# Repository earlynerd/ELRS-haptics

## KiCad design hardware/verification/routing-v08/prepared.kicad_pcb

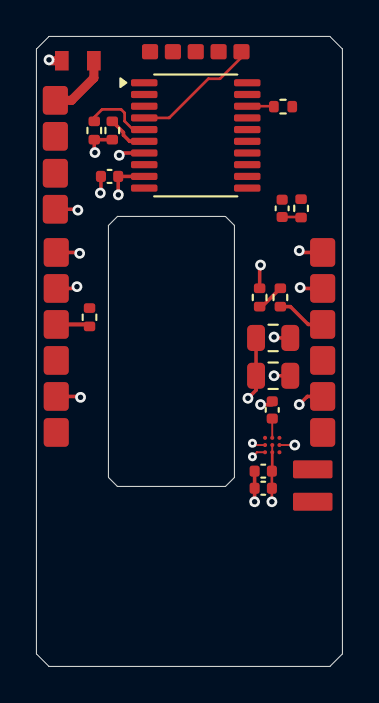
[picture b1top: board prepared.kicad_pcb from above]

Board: 4 copper layers, 17.0 x 35.0 mm, 23 parts (0 on the bottom side), 16 nets.

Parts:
C23, C24, C160: 100n; C_0402_1005Metric
C25: 1u; C_0402_1005Metric
C161: 10u; C_0805_2012Metric
C162: 10n; C_0402_1005Metric
C163: 22u 10V X5R; C_0805_2012Metric
F106: 250mA FAST; Fuse_Littelfuse_467_0603
J124: CHAIN IN; WirePads_6_P2mm
J125: CHAIN OUT; WirePads_6_P2mm
J126: ICE / INITIAL FLASH; WirePads_5_P1.27mm
J127: NTC (optional); WirePads_2_P2mm
J206: PROTECTED CELL 90mAh; WirePads_2_P2mm
M7: VLV041235L; Vybronics_VLV041235L_FPC_Contact_Draft
R20, R21: 4.7k; R_0402_1005Metric
R160: 0; R_0402_1005Metric
R161: 33; R_0402_1005Metric
R162, R163: 100k; R_0402_1005Metric
R165: 10k 1%; R_0402_1005Metric
U9: DRV2625; DRV2625_YFF_9_0.4mm
U24: M2003FC1AE; TSSOP-20_4.4x6.5mm_P0.65mm

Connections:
/Eight ring pods/Pod 6 / U24/CELL_POS: F106.1, J206.1
/Eight ring pods/Pod 6 / U24/CELL_TEMP: C162.1, J127.1, R165.2, U24.2
/Eight ring pods/Pod 6 / U24/DRV_REG: C24.1, U9.A2
/Eight ring pods/Pod 6 / U24/LOCAL_SCL: R21.2, U9.C1, U24.6
/Eight ring pods/Pod 6 / U24/LOCAL_SDA: R20.2, U9.B1, U24.5
/Eight ring pods/Pod 6 / U24/LRA_N: M7.2, U9.C3
/Eight ring pods/Pod 6 / U24/LRA_P: M7.1, U9.A3
/Eight ring pods/Pod 6 / U24/UART_RX_LOCAL: J126.4, R160.2, R162.2, U24.18
/Eight ring pods/Pod 6 / U24/UART_TX_LOCAL: J126.3, R161.1, R163.2, U24.8
GND: C23.2, C24.2, C25.2, C160.2, C161.2, C162.2, C163.2, J124.2, J125.2, J126.2, J127.2, J206.2, U9.B3, U24.7
POD_3V3: C23.1, C25.1, C160.1, C161.1, C163.1, J124.1, J125.1, J126.1, R20.1, R21.1, R162.1, R163.1, R165.1, U9.B2, U9.C2, U24.9
RING_D6: J124.3, R160.1
RING_D7: J125.3, R161.2
RING_RETURN: J124.6, J125.6
RING_nRESET: J124.4, J125.4, J126.5, U24.4
VBAT: F106.2, J124.5, J125.5

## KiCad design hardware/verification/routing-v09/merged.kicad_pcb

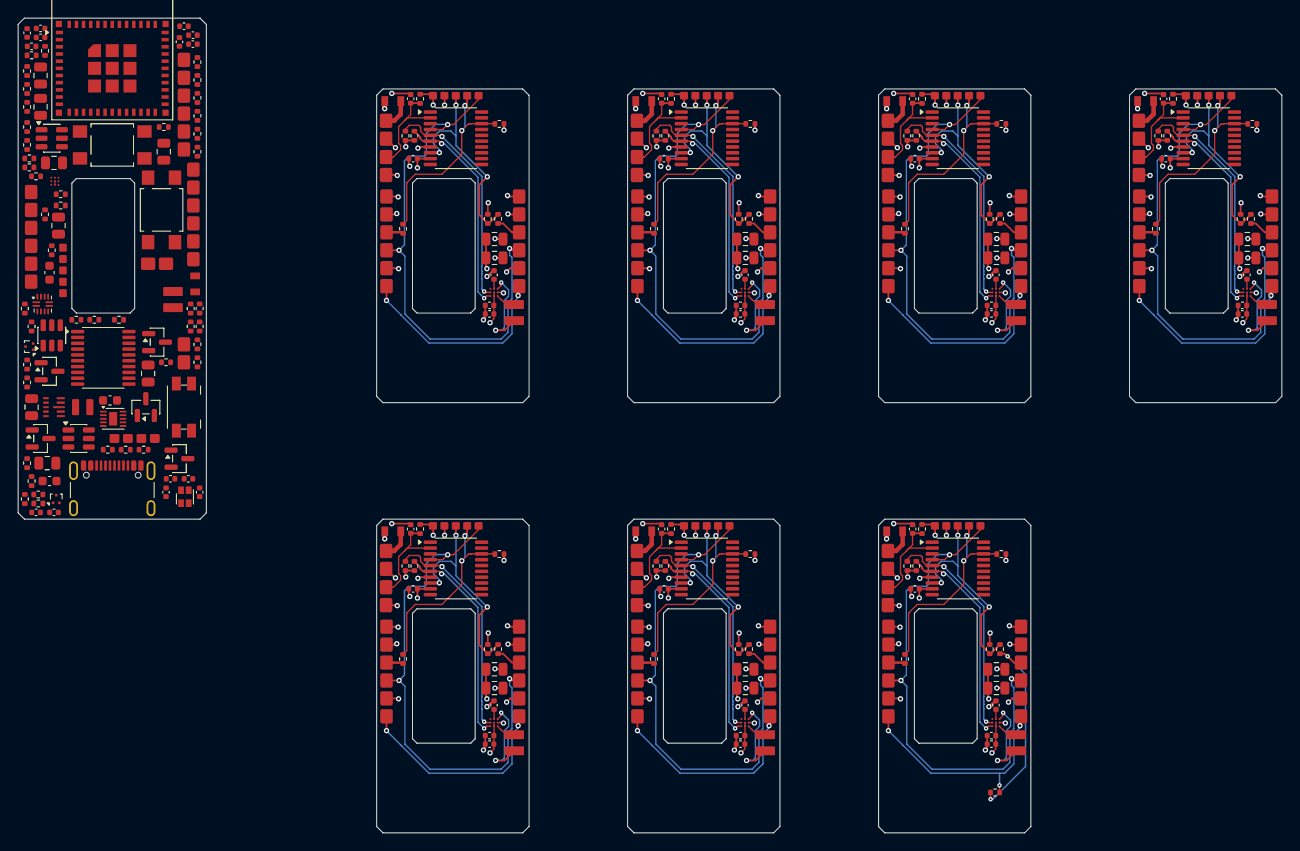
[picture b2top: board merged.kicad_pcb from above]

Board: 4 copper layers, 141.0 x 90.9 mm, 261 parts (0 on the bottom side), 133 nets.

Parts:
C1, C7, C10, C13, C16, C19, C22, C25, C28, C41, C43: 1u; C_0402_1005Metric
C2, C5, C6, C8, C9, C11, C12, C14, C15, C17, C18, C20, C21, C23, C24, C26, C27, C31, C100, C110, C120, C130, C140, C150, C160, C170: 100n; C_0402_1005Metric
C3, C101, C111, C121, C131, C141, C151, C161, C171: 10u; C_0805_2012Metric
C29, C30: TUNE / DNP; C_0402_1005Metric
C32, C34, C36: 1u 10V; C_0603_1608Metric
C33: 100n 10V; C_0402_1005Metric
C35, C37, C40: 10u 10V; C_0805_2012Metric
C38, C39: 22u 10V; C_0805_2012Metric
C42: 4.7n 25V; C_0402_1005Metric
C102, C112, C122, C132, C142, C152, C162, C172: 10n; C_0402_1005Metric
C103, C113, C123, C133, C143, C153, C163, C173: 22u 10V X5R; C_0805_2012Metric
D1: LTST-C19HE1WT; LED_LiteOn_LTST-C19HE1WT
F100, F101, F102, F103, F104, F105, F106, F107: 250mA FAST; Fuse_Littelfuse_467_0603
J1: ESP UART / BOOT / RESET; WirePads_6_P2mm
J2: USB4105-GF-A; USB_C_Receptacle_GCT_USB4105-xx-A_16P_TopMnt_Horizontal
J3: VBAT BUS + NTC; WirePads_4_P1.5mm
J100, J104, J108, J112, J116, J120, J124, J128: CHAIN IN; WirePads_6_P2mm
J101, J105, J109, J113, J117, J121, J125, J129: CHAIN OUT; WirePads_6_P2mm
J102, J106, J110, J114, J118, J122, J126, J130: ICE / INITIAL FLASH; WirePads_5_P1.27mm
J103, J107, J111, J115, J119, J123, J127, J131: NTC (optional); WirePads_2_P2mm
J200, J201, J202, J203, J204, J205, J206, J207: PROTECTED CELL 90mAh; WirePads_2_P2mm
L1: 0.47uH; L_Murata_DFE201612E
M1, M2, M3, M4, M5, M6, M7, M8: VLV041235L; Vybronics_VLV041235L_FPC_Contact_Draft
Q1, Q2, Q3, Q4, Q5: 2N7002; SOT-23
R1, R2, R8, R9, R10, R11, R12, R13, R14, R15, R16, R17, R18, R19, R20, R21, R22, R23: 4.7k; R_0402_1005Metric
R3, R4, R5, R6, R27, R36, R37: 10k; R_0402_1005Metric
R7, R30, R31, R32, R33, R34, R38, R39, R43, R45, R48, R50, R52, R102, R103, R112, R113, R122, R123, R132, R133, R142, R143, R152, R153, R162, R163, R172, R173: 100k; R_0402_1005Metric
R24, R25: 22; R_0402_1005Metric
R26: 887k 1%; R_0402_1005Metric
R28: 62k 1%; R_0402_1005Metric
R29: 43k 1%; R_0402_1005Metric
R35: 1M; R_0402_1005Metric
R40: 511k 1%; R_0402_1005Metric
R41: 91k 1%; R_0402_1005Metric
R42, R101, R111, R121, R131, R141, R151, R161, R171: 33; R_0402_1005Metric
R44, R46: 100; R_0402_1005Metric
R47, R49, R51: 2.2k; R_0402_1005Metric
R53, R100, R110, R120, R130, R140, R150, R160, R170: 0; R_0402_1005Metric
R105, R115, R125, R135, R145, R155, R165, R175: 10k 1%; R_0402_1005Metric
SW1: ESP RESET; SW_SPST_TL3305A
SW2: ESP BOOT; SW_SPST_TL3305A
SW3: WAKE / SHIP; Panasonic_EVQPUJ_EVQPUA
U1: ESP32-C6-MINI-1
U3, U4, U5, U6, U7, U8, U9, U10: DRV2625; DRV2625_YFF_9_0.4mm
U11: BQ25186DLH; Texas_DLH0010A_WSON-10-1EP_2.2x2mm_P0.4mm_EP0.9x1.5mm
U12: TPS63802DLA; TPS63802_DLA0010A
U13: TUSB320LAIRWB; Texas_X2QFN-12_1.6x1.6mm_P0.4mm
U14, U15: TPD2EUSB30; Texas_DRT-3
U16: TPS2553DBV; SOT-23-6
U17: TS5A3159DBV; SOT-23-6
U18, U19, U20, U21, U22, U23, U24, U25: M2003FC1AE; TSSOP-20_4.4x6.5mm_P0.65mm
U26: TPS22918DBV; SOT-23-6

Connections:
3V3: C2.1, C3.1, C31.1, C38.1, C39.1, C41.1, D1.4, J1.1, R1.1, R2.1, R3.1, R4.1, R5.1, R27.1, R36.1, R37.1, R40.1, R48.1, R50.1, R52.1, U1.3, U12.6, U13.12, U26.1
/Charger and regulated supply/CHG_nCE: Q1.3, R38.2, U11.4
/Charger and regulated supply/PACK_TS: J3.3, SW3.1, U11.6
/Charger and regulated supply/REG_FB: R40.2, R41.1, U12.4
/Charger and regulated supply/SW_L1: L1.1, U12.9
/Charger and regulated supply/SW_L2: L1.2, U12.7
/Charger and regulated supply/SYS: C35.1, C37.1, R38.1, U11.1, U12.1, U12.10
/ESP reset, boot and decoupling/LED_B_K: D1.3, R51.2
/ESP reset, boot and decoupling/LED_G_K: D1.2, R49.2
/ESP reset, boot and decoupling/LED_R_K: D1.1, R47.2
/Eight ring pods/Pod 0 / U18/CELL_POS: F100.1, J200.1
/Eight ring pods/Pod 0 / U18/CELL_TEMP: C102.1, J103.1, R105.2, U18.2
/Eight ring pods/Pod 0 / U18/DRV_REG: C6.1, U3.A2
/Eight ring pods/Pod 0 / U18/LOCAL_SCL: R9.2, U3.C1, U18.6
/Eight ring pods/Pod 0 / U18/LOCAL_SDA: R8.2, U3.B1, U18.5
/Eight ring pods/Pod 0 / U18/LRA_N: M1.2, U3.C3
/Eight ring pods/Pod 0 / U18/LRA_P: M1.1, U3.A3
/Eight ring pods/Pod 0 / U18/UART_RX_LOCAL: J102.4, R100.2, R102.2, U18.18
/Eight ring pods/Pod 0 / U18/UART_TX_LOCAL: J102.3, R101.1, R103.2, U18.8
/Eight ring pods/Pod 1 / U19/CELL_POS: F101.1, J201.1
/Eight ring pods/Pod 1 / U19/CELL_TEMP: C112.1, J107.1, R115.2, U19.2
/Eight ring pods/Pod 1 / U19/DRV_REG: C9.1, U4.A2
/Eight ring pods/Pod 1 / U19/LOCAL_SCL: R11.2, U4.C1, U19.6
/Eight ring pods/Pod 1 / U19/LOCAL_SDA: R10.2, U4.B1, U19.5
/Eight ring pods/Pod 1 / U19/LRA_N: M2.2, U4.C3
/Eight ring pods/Pod 1 / U19/LRA_P: M2.1, U4.A3
/Eight ring pods/Pod 1 / U19/UART_RX_LOCAL: J106.4, R110.2, R112.2, U19.18
/Eight ring pods/Pod 1 / U19/UART_TX_LOCAL: J106.3, R111.1, R113.2, U19.8
/Eight ring pods/Pod 2 / U20/CELL_POS: F102.1, J202.1
/Eight ring pods/Pod 2 / U20/CELL_TEMP: C122.1, J111.1, R125.2, U20.2
/Eight ring pods/Pod 2 / U20/DRV_REG: C12.1, U5.A2
/Eight ring pods/Pod 2 / U20/LOCAL_SCL: R13.2, U5.C1, U20.6
/Eight ring pods/Pod 2 / U20/LOCAL_SDA: R12.2, U5.B1, U20.5
/Eight ring pods/Pod 2 / U20/LRA_N: M3.2, U5.C3
/Eight ring pods/Pod 2 / U20/LRA_P: M3.1, U5.A3
/Eight ring pods/Pod 2 / U20/UART_RX_LOCAL: J110.4, R120.2, R122.2, U20.18
/Eight ring pods/Pod 2 / U20/UART_TX_LOCAL: J110.3, R121.1, R123.2, U20.8
/Eight ring pods/Pod 3 / U21/CELL_POS: F103.1, J203.1
/Eight ring pods/Pod 3 / U21/CELL_TEMP: C132.1, J115.1, R135.2, U21.2
/Eight ring pods/Pod 3 / U21/DRV_REG: C15.1, U6.A2
/Eight ring pods/Pod 3 / U21/LOCAL_SCL: R15.2, U6.C1, U21.6
/Eight ring pods/Pod 3 / U21/LOCAL_SDA: R14.2, U6.B1, U21.5
/Eight ring pods/Pod 3 / U21/LRA_N: M4.2, U6.C3
/Eight ring pods/Pod 3 / U21/LRA_P: M4.1, U6.A3
/Eight ring pods/Pod 3 / U21/UART_RX_LOCAL: J114.4, R130.2, R132.2, U21.18
/Eight ring pods/Pod 3 / U21/UART_TX_LOCAL: J114.3, R131.1, R133.2, U21.8
/Eight ring pods/Pod 4 / U22/CELL_POS: F104.1, J204.1
/Eight ring pods/Pod 4 / U22/CELL_TEMP: C142.1, J119.1, R145.2, U22.2
/Eight ring pods/Pod 4 / U22/DRV_REG: C18.1, U7.A2
/Eight ring pods/Pod 4 / U22/LOCAL_SCL: R17.2, U7.C1, U22.6
/Eight ring pods/Pod 4 / U22/LOCAL_SDA: R16.2, U7.B1, U22.5
/Eight ring pods/Pod 4 / U22/LRA_N: M5.2, U7.C3
/Eight ring pods/Pod 4 / U22/LRA_P: M5.1, U7.A3
/Eight ring pods/Pod 4 / U22/UART_RX_LOCAL: J118.4, R140.2, R142.2, U22.18
/Eight ring pods/Pod 4 / U22/UART_TX_LOCAL: J118.3, R141.1, R143.2, U22.8
/Eight ring pods/Pod 5 / U23/CELL_POS: F105.1, J205.1
/Eight ring pods/Pod 5 / U23/CELL_TEMP: C152.1, J123.1, R155.2, U23.2
/Eight ring pods/Pod 5 / U23/DRV_REG: C21.1, U8.A2
/Eight ring pods/Pod 5 / U23/LOCAL_SCL: R19.2, U8.C1, U23.6
/Eight ring pods/Pod 5 / U23/LOCAL_SDA: R18.2, U8.B1, U23.5
/Eight ring pods/Pod 5 / U23/LRA_N: M6.2, U8.C3
/Eight ring pods/Pod 5 / U23/LRA_P: M6.1, U8.A3
/Eight ring pods/Pod 5 / U23/UART_RX_LOCAL: J122.4, R150.2, R152.2, U23.18
/Eight ring pods/Pod 5 / U23/UART_TX_LOCAL: J122.3, R151.1, R153.2, U23.8
/Eight ring pods/Pod 6 / U24/CELL_POS: F106.1, J206.1
/Eight ring pods/Pod 6 / U24/CELL_TEMP: C162.1, J127.1, R165.2, U24.2
/Eight ring pods/Pod 6 / U24/DRV_REG: C24.1, U9.A2
/Eight ring pods/Pod 6 / U24/LOCAL_SCL: R21.2, U9.C1, U24.6
/Eight ring pods/Pod 6 / U24/LOCAL_SDA: R20.2, U9.B1, U24.5
/Eight ring pods/Pod 6 / U24/LRA_N: M7.2, U9.C3
/Eight ring pods/Pod 6 / U24/LRA_P: M7.1, U9.A3
/Eight ring pods/Pod 6 / U24/UART_RX_LOCAL: J126.4, R160.2, R162.2, U24.18
/Eight ring pods/Pod 6 / U24/UART_TX_LOCAL: J126.3, R161.1, R163.2, U24.8
/Eight ring pods/Pod 7 / U25/CELL_POS: F107.1, J207.1
/Eight ring pods/Pod 7 / U25/CELL_TEMP: C172.1, J131.1, R175.2, U25.2
/Eight ring pods/Pod 7 / U25/DRV_REG: C27.1, U10.A2
/Eight ring pods/Pod 7 / U25/LOCAL_SCL: R23.2, U10.C1, U25.6
/Eight ring pods/Pod 7 / U25/LOCAL_SDA: R22.2, U10.B1, U25.5
/Eight ring pods/Pod 7 / U25/LRA_N: M8.2, U10.C3
/Eight ring pods/Pod 7 / U25/LRA_P: M8.1, U10.A3
/Eight ring pods/Pod 7 / U25/UART_RX_LOCAL: J130.4, R170.2, R172.2, U25.18
/Eight ring pods/Pod 7 / U25/UART_TX_LOCAL: J130.3, R171.1, R173.2, U25.8
/POD_QOD: R46.2, U26.5
/POD_SLEW: C42.1, U26.4
/RESET_D: Q5.3, R44.2
/RING_TX_MCU: R42.1, R43.1, U1.25
/USB-C data and power/CC1: J2.A5, U13.1, U15.1
/USB-C data and power/CC2: J2.B5, U13.2, U15.2
/USB-C data and power/CC_VBUS_DET: R26.2, U13.4
/USB-C data and power/ILIM_HIGH_D: Q3.3, R29.2
/USB-C data and power/ILIM_R: R28.1, R29.1, U17.1
/USB-C data and power/ILIM_SELECT: U16.5, U17.4
/USB-C data and power/USB_CONN_N: J2.A7, J2.B7, R24.1, U14.2
/USB-C data and power/USB_CONN_P: J2.A6, J2.B6, R25.1, U14.1
/USB-C data and power/USB_IN_EN: Q2.3, R32.2, U16.3
/USB-C data and power/VBUS: C32.1, C33.1, J2.A4, J2.A9, J2.B4, J2.B9, R26.1, R32.1, R34.1, U16.1, U17.3, U17.5
/USB-C data and power/VBUS_GATE: Q4.1, R34.2, R35.1
BOOT_IO8: R4.2, U1.22
BOOT_IO9: J1.5, R5.2, SW2.1, U1.23
CC_nINT: R27.2, U1.12, U13.6
CHG_ALLOW: Q1.1, R39.1, U1.26
CHG_nINT: R37.2, U1.27, U11.9
GND: C1.2, C2.2, C3.2, C5.2, C6.2, C7.2, C8.2, C9.2, C10.2, C11.2, C12.2, C13.2, C14.2, C15.2, C16.2, C17.2, C18.2, C19.2, C20.2, C21.2, C22.2, C23.2, C24.2, C25.2, C26.2, C27.2, C28.2, C29.2, C30.2, C31.2, C32.2, C33.2, C34.2, C35.2, C36.2, C37.2, C38.2, C39.2, C40.2, C41.2, C42.2, C43.2, C100.2, C101.2, C102.2, C103.2, C110.2, C111.2, C112.2, C113.2, C120.2, C121.2, C122.2, C123.2, C130.2, C131.2, C132.2, C133.2, C140.2, C141.2, C142.2, C143.2, C150.2, C151.2, C152.2, C153.2, C160.2, C161.2, C162.2, C163.2, C170.2, C171.2, C172.2, C173.2, J1.2, J2.A1, J2.A12, J2.B1, J2.B12, J2.SH, J3.2, J3.4, J100.2, J101.2, J102.2, J103.2, J104.2, J105.2, J106.2, J107.2, J108.2, J109.2, J110.2, J111.2, J112.2, J113.2, J114.2, J115.2, J116.2, J117.2, J118.2, J119.2, J120.2, J121.2, J122.2, J123.2, J124.2, J125.2, J126.2, J127.2, J128.2, J129.2, J130.2, J131.2, J200.2, J201.2, J202.2, J203.2, J204.2, J205.2, J206.2, J207.2, Q1.2, Q2.2, Q3.2, Q4.2, Q5.2, R7.2, R28.2, R30.2, R31.2, R33.2, R35.2, R39.2, R41.2, R43.2, R45.2, SW1.2, SW2.2, SW3.2, U1.1, U1.2, U1.11, U1.14, U1.36, U1.37, U1.38, U1.39, U1.40, U1.41, U1.42, U1.43, U1.44, U1.45, U1.46, U1.47, U1.48, U1.49, U1.50, U1.51, U1.52, U1.53, U3.B3, U4.B3, U5.B3, U6.B3, U7.B3, U8.B3, U9.B3, U10.B3, U11.5, U11.11, U12.2, U12.3, U12.8, U13.3, U13.5, U13.10, U13.11, U14.3, U15.3, U16.2, U17.2, U18.7, U19.7, U20.7, U21.7, U22.7, U23.7, U24.7, U25.7, U26.2
I2C_SCL: R2.2, U1.16, U11.8, U13.8
I2C_SDA: R1.2, U1.15, U11.7, U13.7
LED_B_N: R51.1, R52.2, U1.20
LED_G_N: R49.1, R50.2, U1.10
LED_R_N: R47.1, R48.2, U1.9
MCU_EN: C1.1, J1.6, R3.2, SW1.1, U1.8
POD_3V3: C5.1, C7.1, C8.1, C10.1, C11.1, C13.1, C14.1, C16.1, C17.1, C19.1, C20.1, C22.1, C23.1, C25.1, C26.1, C28.1, C43.1, C100.1, C101.1, C103.1, C110.1, C111.1, C113.1, C120.1, C121.1, C123.1, C130.1, C131.1, C133.1, C140.1, C141.1, C143.1, C150.1, C151.1, C153.1, C160.1, C161.1, C163.1, C170.1, C171.1, C173.1, J100.1, J101.1, J102.1, J104.1, J105.1, J106.1, J108.1, J109.1, J110.1, J112.1, J113.1, J114.1, J116.1, J117.1, J118.1, J120.1, J121.1, J122.1, J124.1, J125.1, J126.1, J128.1, J129.1, J130.1, R6.1, R8.1, R9.1, R10.1, R11.1, R12.1, R13.1, R14.1, R15.1, R16.1, R17.1, R18.1, R19.1, R20.1, R21.1, R22.1, R23.1, R46.1, R102.1, R103.1, R105.1, R112.1, R113.1, R115.1, R122.1, R123.1, R125.1, R132.1, R133.1, R135.1, R142.1, R143.1, R145.1, R152.1, R153.1, R155.1, R162.1, R163.1, R165.1, R172.1, R173.1, R175.1, U3.B2, U3.C2, U4.B2, U4.C2, U5.B2, U5.C2, U6.B2, U6.C2, U7.B2, U7.C2, U8.B2, U8.C2, U9.B2, U9.C2, U10.B2, U10.C2, U18.9, U19.9, U20.9, U21.9, U22.9, U23.9, U24.9, U25.9, U26.6
POD_POWER_ON: R45.1, U1.6, U26.3
RING_D0: J100.3, R42.2, R100.1
RING_D1: J101.3, J104.3, R101.2, R110.1
RING_D2: J105.3, J108.3, R111.2, R120.1
RING_D3: J109.3, J112.3, R121.2, R130.1
RING_D4: J113.3, J116.3, R131.2, R140.1
RING_D5: J117.3, J120.3, R141.2, R150.1
RING_D6: J121.3, J124.3, R151.2, R160.1
RING_D7: J125.3, J128.3, R161.2, R170.1
RING_D8: J129.3, R53.1, R171.2
RING_RESET_ASSERT: Q5.1, R7.1, U1.24
RING_RETURN: J100.6, J101.6, J104.6, J105.6, J108.6, J109.6, J112.6, J113.6, J116.6, J117.6, J120.6, J121.6, J124.6, J125.6, J128.6, J129.6, R53.2, U1.5
RING_nRESET: C40.1, J100.4, J101.4, J102.5, J104.4, J105.4, J106.5, J108.4, J109.4, J110.5, J112.4, J113.4, J114.5, J116.4, J117.4, J118.5, J120.4, J121.4, J122.5, J124.4, J125.4, J126.5, J128.4, J129.4, J130.5, R6.2, R44.1, U18.4, U19.4, U20.4, U21.4, U22.4, U23.4, U24.4, U25.4
UART_RX: J1.4, U1.30
UART_TX: J1.3, U1.31
USB_5V_LIMITED: C34.1, U11.10, U16.6
USB_D_N: C29.1, R24.2, U1.17
USB_D_P: C30.1, R25.2, U1.18
USB_INPUT_OFF: Q2.1, R33.1, U1.19
USB_LIMIT_ENABLE: R31.1, U1.28, U17.6
USB_LIMIT_HIGH: Q3.1, R30.1, U1.29
VBAT: C36.1, F100.2, F101.2, F102.2, F103.2, F104.2, F105.2, F106.2, F107.2, J3.1, J100.5, J101.5, J104.5, J105.5, J108.5, J109.5, J112.5, J113.5, J116.5, J117.5, J120.5, J121.5, J124.5, J125.5, J128.5, J129.5, U11.2
VBUS_nPRESENT: Q4.3, R36.2, U1.13
